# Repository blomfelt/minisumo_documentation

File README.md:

# CRF minisumo++2027 (CRFminisumoplusplus2027)

A follow-up to the [CRF SumoBot](https://github.com/ChalmersRobotics/CRF-SumoBot)[^1] designed primarily by Kalle Strålman and David Strålman.

After RobotSM 2026 we sold out of kits that were arduino based and ran out of batteries that were cheap. While doing these changes we also chose to update the PCB and make some pretty big changes to the model, so why not make upgrades!?

## Concept for minisumo++2027
A minisumo .. plus some other things .. plus even some more!
- Minisumo for robotSM primarily, but as possible a module that can be a spring board into other things
- Minisumo that one steers like an RC car via bluetooth!
- Lego version! .. encapsulate motors and such into a robot combat like (or autonomous robot?) that can be lego'd together!
- [Death racers](https://www.youtube.com/watch?v=i10rxmsKHts)
- Robot combat base module
- More? Why not?? Probably possible
  - Line following!?
  - Esphome controlled robot w/ or w/o home assistant!?

## Goals and features
1. Good for beginners to meet the primary goal of minisumo for robotSM
2. Cheap as chips
3. Possibility to make really really smallish, for example to encapsulate into lego!
4. More voltage to motors!
5. Battery charging possible since using the c6!
6. Possibility to expand and reuse gpio's or other purpose robots!

## TODO
- [x] Choose wires or PCB for connection (PCB right now)
- [x] Add sensors
- [x] Add Sumo-code
- [x] Add bluetooth code
- [x] Control motors via bluetooth
- [ ] Design the chassis
- [ ] Write build instructions
- [ ] PCBs - need to build to confirm eg ALL footprints (all done by hand) && perform functional tests with everything mounted as designed with software running && confirm within eventual 3d packaging.

## Instructions
- Obtain Components and Chassis (See *Bill of Materials below*) or via a kit @ CRF while supplies last!
- Download the `minisumo-bot.ino` file from [releases on the right side](https://github.com/ChalmersRobotics/minisumoplusplus2027/releases)
- Build the robot according to the [instructions](TODO)
- Upload the code to the robot as in the [instructions](TODO) or as documented below.

### Instructions for pcb assembly / soldering incl tips and tricks
tbd

### Instructions for final assembly
tbd

### Instructions for uploading code to the ESP32
- Install Arduino IDE v2 from their [website](https://docs.arduino.cc/software/ide-v2/tutorials/getting-started/ide-v2-downloading-and-installing/)[^2] or your favourite package manager. Current version is 2.3.10.
- Install the required boards from the Boards Manager in the left column, second icon from the top:
    - esp32 by Espressif Systems (current version 3.3.11)
- Install the required libraries from the Library Manager, icon under the Boards Manager (or via Tools > Manage Libraries):
    - "NimBLE_Arduino" by h2zero (current version 2.5.1)
    - "HCSR04" by Martin Sosic (current version 2.0.0)
- Choose the correct board from the Select Board dropdown > Select other board and port. Then Search for *MakerGO ESP32 C6 SuperMini*. It will look as if nothing happens but that is fine.
- Connect the ESP32 to your computer while holding the BOOT button on the board. It will show up in the right column as something like `/dev/usb/ttyASM0` if you are on linux. Click Ok.
    - The board may not show up, in which case you need to hold the Boot button while connecting the board, then tapping the RST button and finally releasing the BOOT button.
- Paste the contents of `minisumo-bot.ino` into the default sketch or download the file and open it from File > Open
- Verify and/or Upload the sketch to the ESP32 using the checkbox and/or arrow in the top left corner.

### Bill of Materials
See [the google sheets bom](https://docs.google.com/spreadsheets/d/1KNLTKy2cLUtDrH-E30Gfz_4ahhQaqS2SGsFHG1Fw9_M/edit?usp=sharing))
- PCB
- 3D printed chassis
- [ESP32 C6 Super Mini](https://mischianti.org/esp32-c6-supermini-high-resolution-pinout-datasheet-schema-and-specs/)
- Battery 3.7v cr123 with recharge usb c contact built in!
- Battery contacts!
- Buck boost to push motor driver to 9v!
- Switch on / off .. a smaller one is needed
- Motor driver: L298N
- Ultrasonic sensor: HC-SR04
- IR sensor: v183
- Start module
- Cables

## Changelog

| Version       | Changes      |
| ------------- | ------------- |
| v1.0          | First draft |

## References
[^1]: CRF SumoBot, Kalle Strålman, [https://github.com/ChalmersRobotics/CRF-SumoBot](https://github.com/ChalmersRobotics/CRF-SumoBot)
[^2]: Downloading and installing the Arduino IDE 2, Arduino, [https://docs.arduino.cc/software/ide-v2/tutorials/getting-started/ide-v2-downloading-and-installing/](https://docs.arduino.cc/software/ide-v2/tutorials/getting-started/ide-v2-downloading-and-installing/)

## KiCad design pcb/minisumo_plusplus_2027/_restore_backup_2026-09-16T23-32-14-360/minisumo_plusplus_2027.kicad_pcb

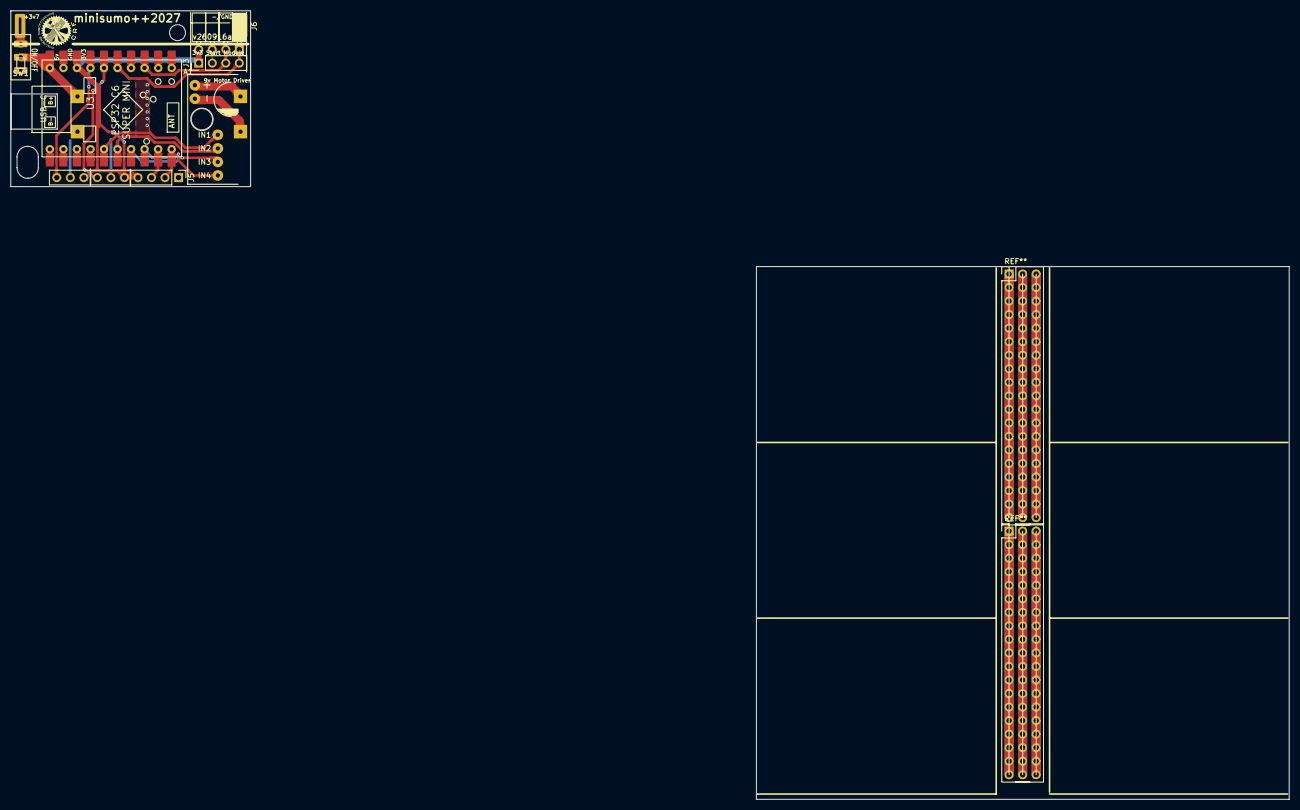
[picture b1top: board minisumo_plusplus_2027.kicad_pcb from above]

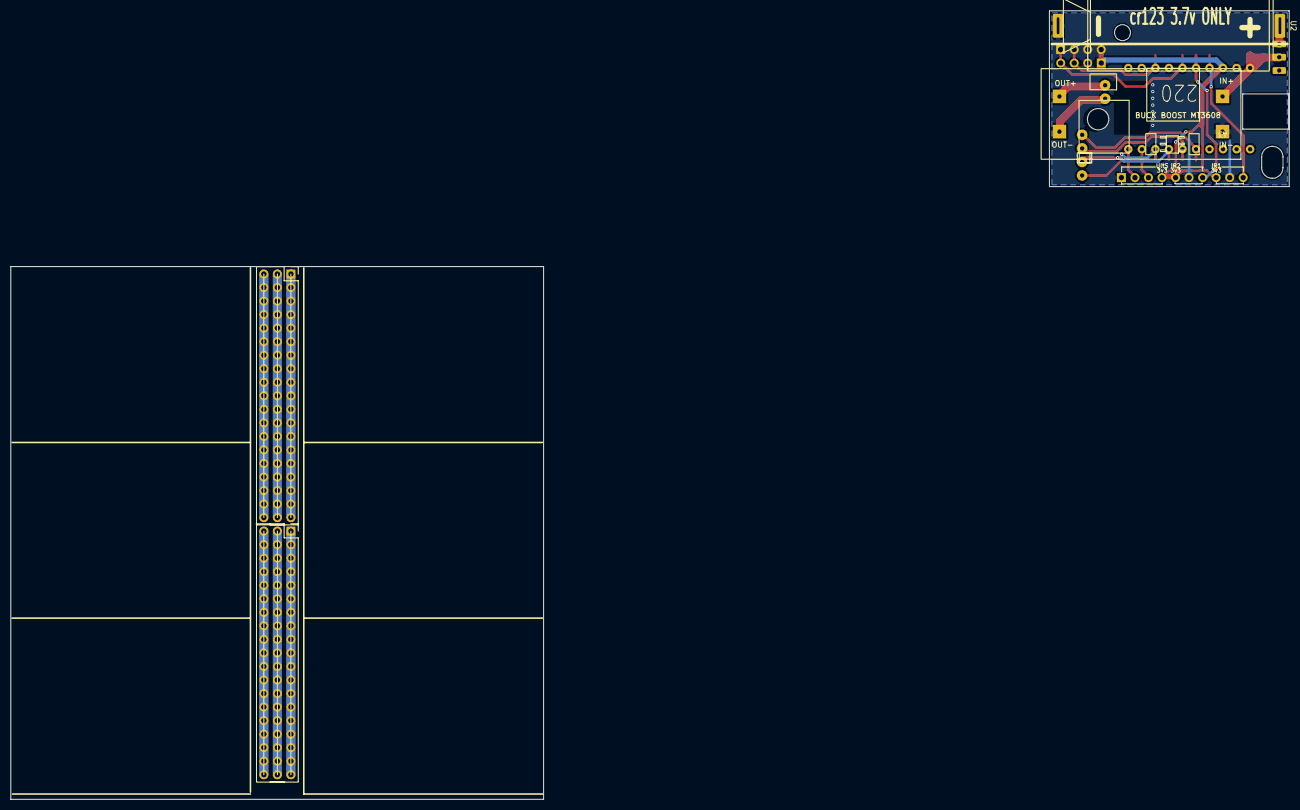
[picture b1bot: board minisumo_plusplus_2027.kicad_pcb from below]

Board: 2 copper layers, 45.0 x 33.0 mm, 8 parts (2 on the bottom side), 16 nets.

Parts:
A1: Mini_L298N_2_Channel_H_Bridge_DC_Motor_Driver_Board_with_MX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
A3: MT3608 DC-DC Boost Module – 28V 2A Step-Up Power Module
J3: Start Module - Conn_01x04_Pin; PinHeader_1x04_P2.54mm_Vertical
J5: Conn_01x10_Pin; PinHeader_1x10_P2.54mm_Vertical
J6: Start Module - Conn_01x04_Pin; PinSocket_1x04_P2.54mm_Horizontal
SW1: SW_SPDT; SPST_switch_SS-12D00G4_1P2T_2.5mm_pitch_vert
U2: battery cr123 3.7v with contacts for 18650
U3: ESP32-C6-SuperMini; ESP32-C6-SuperMini_SMD_THT

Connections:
3v3: J3.1, J5.4, J5.5, J5.8, J6.4, U3.3 (3v3)
/3v7 (>3v3 & <5v): A3.1 (IN+), SW1.2 (B), U3.1 (5V)
/9v: A1.1 (pwr), A3.3 (OUT+)
GND: A3.2 (IN-), J3.2, J5.1, J5.6, J5.9, J6.3, U2.2 (-/gnd), U3.2 (GND)
IR Front: J5.10, U3.4 (GPIO20)
IR Rear: J5.7, U3.5 (GPIO19)
unnamed: A1.3 (INT1), U3.15 (GPIO2-A2)
unnamed: A1.4 (INT2), U3.16 (GPIO3-A3)
unnamed: A1.5 (INT3), U3.17 (GPIO4-A4)
unnamed: A1.6 (INT4), U3.18 (GPIO5-A5)
unnamed: A1.2 (gnd), A3.4 (OUT-)
unnamed: SW1.1 (A), U2.1 (+)
START Kill - not mandatory for sumo: J3.4, J6.1, U3.6 (GPIO18)
START Start: J3.3, J6.2, U3.8 (GPIO14)
US Echo Tx: J5.2, U3.20 (GPIO7)
US Trigger Rx: J5.3, U3.19 (GPIO6-A6)
